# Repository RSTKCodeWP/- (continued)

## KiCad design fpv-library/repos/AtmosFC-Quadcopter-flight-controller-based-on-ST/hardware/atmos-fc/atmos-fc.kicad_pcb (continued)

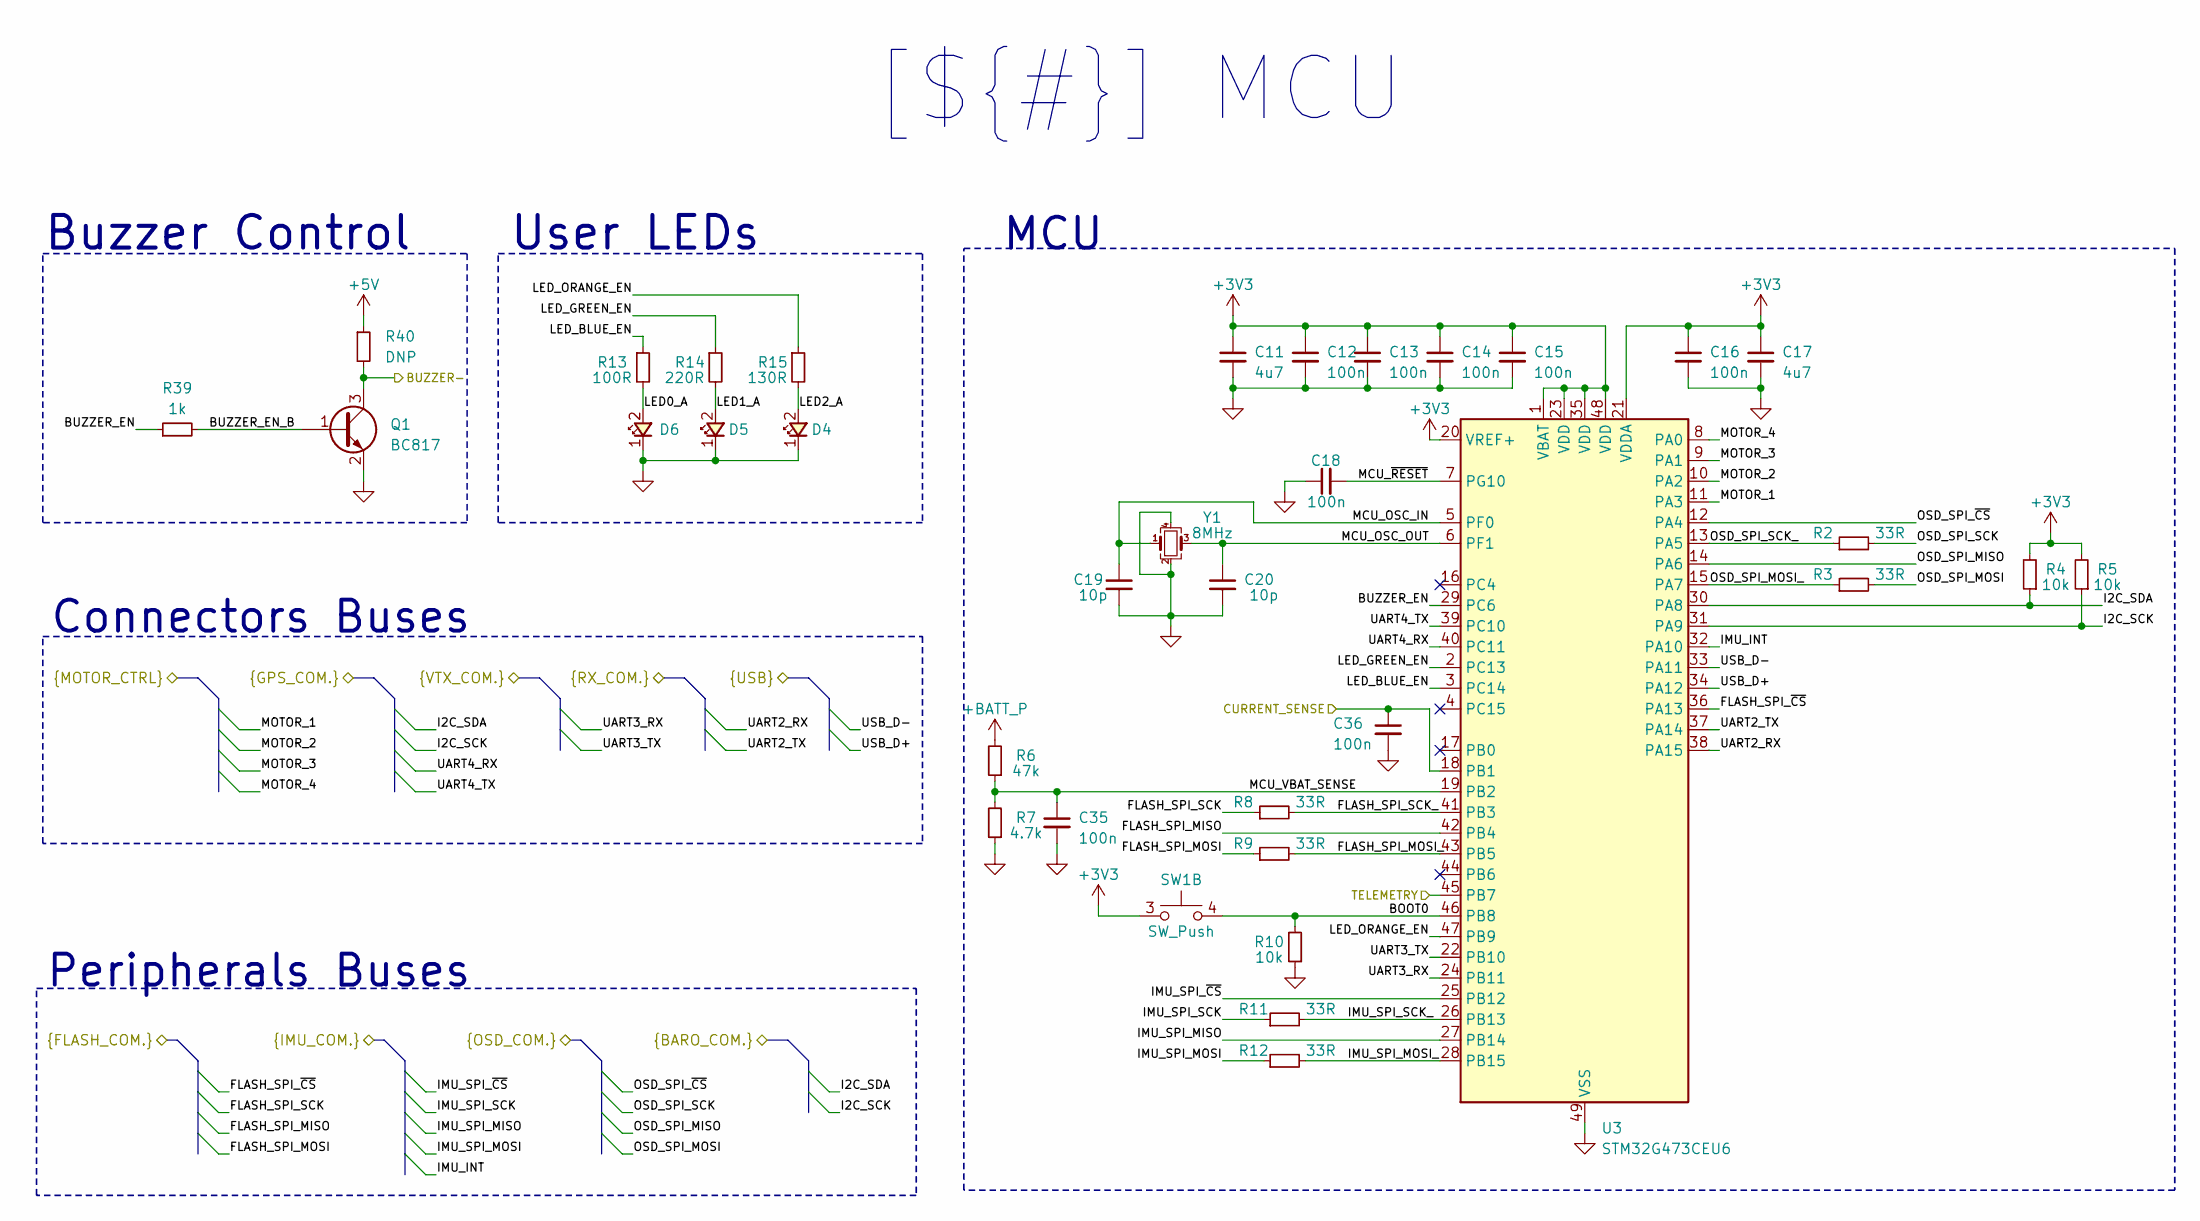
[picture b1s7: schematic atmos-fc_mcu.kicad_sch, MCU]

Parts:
C11, C17: 4u7; C_0603_1608Metric; Mfr Part Number GRM188Z71C475KE21J
C12, C13, C14, C15, C16, C18, C35, C36: 100n; C_0402_1005Metric; Mfr Part Number MSASE105SB7104KFNA01
C19, C20: 10p; C_0402_1005Metric; Mfr Part Number GRM1555C1H100JA01D
D4: LED_0603_1608Metric; Mfr Part Number LO Q976-PS-25
D5: LED_0603_1608Metric; Mfr Part Number LT Q39G-Q1OO-25-1
D6: LED_0603_1608Metric; Mfr Part Number LB Q39G-N1OO-35-1
Q1: BC817; DFN1010D-3; Mfr Part Number BC817-40QBH-QZ
R2, R3, R8, R9, R11, R12: 33R; R_0402_1005Metric; Mfr Part Number CRCW040220K0FKED
R4, R5, R10: 10k; R_0402_1005Metric; Mfr Part Number CRCW040210K0FKEDC
R6: 47k; R_0402_1005Metric; Mfr Part Number CRCW040247K0FKEDC
R7: 4.7k; R_0402_1005Metric; Mfr Part Number CRCW04024K70FKEDC
R13: 100R; R_0402_1005Metric; Mfr Part Number CRCW0402100RFKEDC
R14: 220R; R_0402_1005Metric; Mfr Part Number CRCW0402220RFKED
R15: 130R; R_0402_1005Metric; Mfr Part Number CRCW0402130RFKEDC
R39: 1k; R_0402_1005Metric; Mfr Part Number CRCW04021K00FKED
R40: DNP; R_0402_1005Metric
SW1: SW_Push; Wurth_436331045822; Mfr Part Number 436331045822
U3: STM32G473CEU6; QFN-48-1EP_7x7mm_P0.5mm_EP5.6x5.6mm; Mfr Part Number STM32G473CEU6
Y1: 8MHz; Crystal_SMD_ECS_ECX33_4Pin_3.2x2.5mm; Mfr Part Number ECS-80-10-33-CGN-TR3

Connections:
+3V3: C11.1, C12.1, C13.1, C14.1, C15.1, C16.1, C17.1, R4.2, R5.2, SW1.3 (C), U3.1 (VBAT), U3.20 (VREF+), U3.21 (VDDA), U3.23 (VDD), U3.35 (VDD), U3.48 (VDD); also elsewhere on the board
+5V: R40.1; also elsewhere on the board
+BATT_P: R6.2; also elsewhere on the board
/Connectors/BUZZER-: Q1.3 (C), R40.2; also elsewhere on the board
/Connectors/CURRENT_SENSE: C36.1, U3.18 (PB1); also elsewhere on the board
/Connectors/I2C_SCK: R5.1, U3.31 (PA9); also elsewhere on the board
/Connectors/I2C_SDA: R4.1, U3.30 (PA8); also elsewhere on the board
/Connectors/MOTOR_1: U3.11 (PA3); also elsewhere on the board
/Connectors/MOTOR_2: U3.10 (PA2); also elsewhere on the board
/Connectors/MOTOR_3: U3.9 (PA1); also elsewhere on the board
/Connectors/MOTOR_4: U3.8 (PA0); also elsewhere on the board
/Connectors/TELEMETRY: U3.45 (PB7); also elsewhere on the board
/Connectors/UART2_RX: U3.38 (PA15); also elsewhere on the board
/Connectors/UART2_TX: U3.37 (PA14); also elsewhere on the board
/Connectors/UART3_RX: U3.24 (PB11); also elsewhere on the board
/Connectors/UART3_TX: U3.22 (PB10); also elsewhere on the board
/Connectors/UART4_RX: U3.40 (PC11); also elsewhere on the board
/Connectors/UART4_TX: U3.39 (PC10); also elsewhere on the board
/Connectors/USB_D+: U3.34 (PA12); also elsewhere on the board
/Connectors/USB_D-: U3.33 (PA11); also elsewhere on the board
/Flash Memory/FLASH_SPI_MISO: U3.42 (PB4); also elsewhere on the board
/Flash Memory/FLASH_SPI_MOSI: R9.1; also elsewhere on the board
/Flash Memory/FLASH_SPI_SCK: R8.1; also elsewhere on the board
/Flash Memory/FLASH_SPI_~CS: U3.36 (PA13); also elsewhere on the board
/IMU/IMU_INT: U3.32 (PA10); also elsewhere on the board
/IMU/IMU_SPI_MISO: U3.27 (PB14); also elsewhere on the board
/IMU/IMU_SPI_MOSI: R12.1; also elsewhere on the board
/IMU/IMU_SPI_SCK: R11.1; also elsewhere on the board
/IMU/IMU_SPI_~CS: U3.25 (PB12); also elsewhere on the board
/MCU/BOOT0: R10.2, SW1.4 (D), U3.46 (PB8)
/MCU/BUZZER_EN: R39.1, U3.29 (PC6)
/MCU/BUZZER_EN_B: Q1.1 (B), R39.2
/MCU/FLASH_SPI_MOSI_: R9.2, U3.43 (PB5)
/MCU/FLASH_SPI_SCK_: R8.2, U3.41 (PB3)
/MCU/IMU_SPI_MOSI_: R12.2, U3.28 (PB15)
/MCU/IMU_SPI_SCK_: R11.2, U3.26 (PB13)
/MCU/LED0_A: D6.2, R13.2
/MCU/LED1_A: D5.2, R14.2
/MCU/LED2_A: D4.2, R15.2
/MCU/LED_BLUE_EN: R13.1, U3.3 (PC14)
/MCU/LED_GREEN_EN: R14.1, U3.2 (PC13)
/MCU/LED_ORANGE_EN: R15.1, U3.47 (PB9)
/MCU/MCU_OSC_IN: C19.1, U3.5 (PF0), Y1.1
/MCU/MCU_OSC_OUT: C20.1, U3.6 (PF1), Y1.3
/MCU/MCU_VBAT_SENSE: C35.1, R6.1, R7.2, U3.19 (PB2)
/MCU/MCU_~RESET: C18.2, U3.7 (PG10)
/MCU/OSD_SPI_MISO: U3.14 (PA6); also elsewhere on the board
/MCU/OSD_SPI_MOSI: R3.2; also elsewhere on the board
/MCU/OSD_SPI_MOSI_: R3.1, U3.15 (PA7)
/MCU/OSD_SPI_SCK: R2.2; also elsewhere on the board
/MCU/OSD_SPI_SCK_: R2.1, U3.13 (PA5)
/MCU/OSD_SPI_~CS: U3.12 (PA4); also elsewhere on the board
GND: C11.2, C12.2, C13.2, C14.2, C15.2, C16.2, C17.2, C18.1, C19.2, C20.2, C35.2, C36.2, D4.1, D5.1, D6.1, Q1.2 (E), R7.1, R10.1, U3.49 (VSS), Y1.2, Y1.4; also elsewhere on the board

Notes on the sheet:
[${#}] ${TITLE}
MCU
Peripherals Buses
Buzzer Control
Connectors Buses
User LEDs

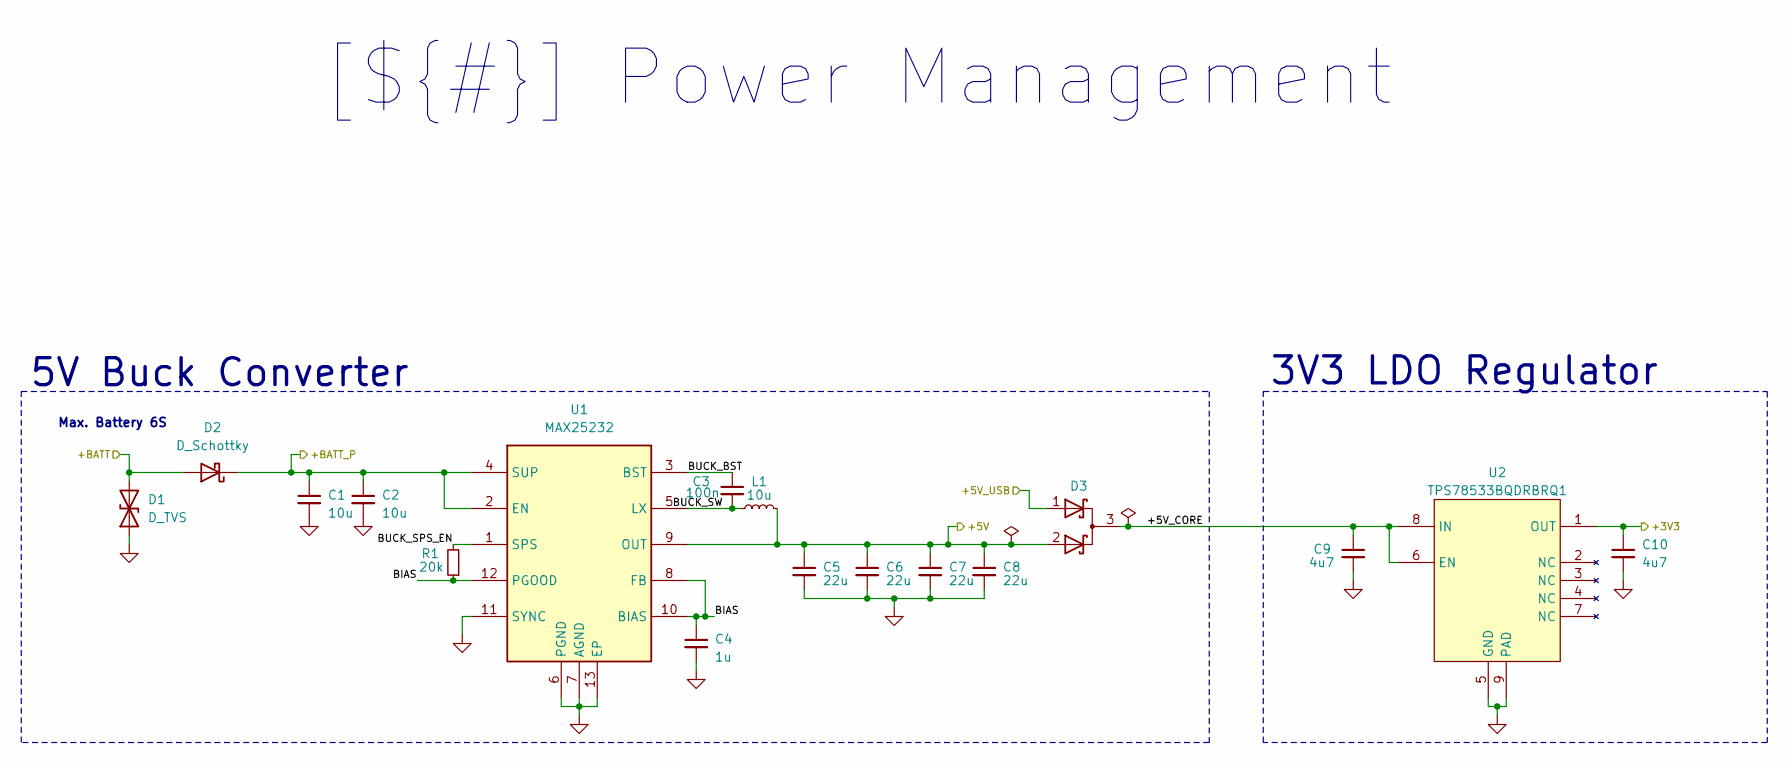
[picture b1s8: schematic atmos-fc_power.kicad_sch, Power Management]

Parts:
C1, C2: 10u; C_1206_3216Metric; Mfr Part Number MCJCG31LBB7106KTPA01
C3: 100n; C_0402_1005Metric; Mfr Part Number MSASE105SB7104KFNA01
C4: 1u; C_0603_1608Metric; Mfr Part Number MSAST168SB7105KTNA01
C5, C6, C7, C8: 22u; C_1206_3216Metric; Mfr Part Number MSASE31LBB7226MTNA01
C9, C10: 4u7; C_0603_1608Metric; Mfr Part Number GRM188Z71C475KE21J
D1: D_TVS; D_SOD-882; Mfr Part Number PESD30VF1BBL-QYL
D2: D_Schottky; DFN3820A; Mfr Part Number V7N103HM3/I
D3: PMEG2020CPASX; HUSON-3-1EP_2x2mm_P1.3mm_EP1.1x1.6mm; Mfr Part Number PMEG2020CPASX
L1: 10u; L_Bourns_SRP5030CC; Mfr Part Number SRP5030CC-100M
R1: 20k; R_0402_1005Metric; Mfr Part Number CRCW040220K0FKED
U1: MAX25232; Maxim_TDFN-12-1EP_3x3mm_P0.5mm_EP1.7x2.5mm_ThermalVias; Mfr Part Number MAX25232ATCD_V+
U2: TPS78533BQDRBRQ1; VSON-8-1EP_3x3mm_P0.65mm_EP1.65x2.4mm_ThermalVias; Mfr Part Number TPS78533BQWDRBRQ1

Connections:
+3V3: C10.1, U2.1 (OUT); also elsewhere on the board
+5V: C5.1, C6.1, C7.1, C8.1, D3.2 (K), L1.2, U1.9 (OUT); also elsewhere on the board
+BATT_P: C1.1, C2.1, D2.1 (K), U1.2 (EN), U1.4 (SUP); also elsewhere on the board
/Connectors/+5V_USB: D3.1 (K); also elsewhere on the board
/Connectors/+BATT: D1.2 (A2), D2.2 (A); also elsewhere on the board
/Power Management/+5V_CORE: C9.1, D3.3 (A), U2.6 (EN), U2.8 (IN)
/Power Management/BIAS: C4.1, R1.1, U1.8 (FB), U1.10 (BIAS), U1.12 (PGOOD)
/Power Management/BUCK_BST: C3.1, U1.3 (BST)
/Power Management/BUCK_SPS_EN: R1.2, U1.1 (SPS)
/Power Management/BUCK_SW: C3.2, L1.1, U1.5 (LX)
GND: C1.2, C2.2, C4.2, C5.2, C6.2, C7.2, C8.2, C9.2, C10.2, D1.1 (A1), U1.6 (PGND), U1.7 (AGND), U1.11 (SYNC), U1.13 (EP), U2.5 (GND), U2.9 (PAD); also elsewhere on the board

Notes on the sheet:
[${#}] ${TITLE}
5V Buck Converter
3V3 LDO Regulator
Max. Battery 6S

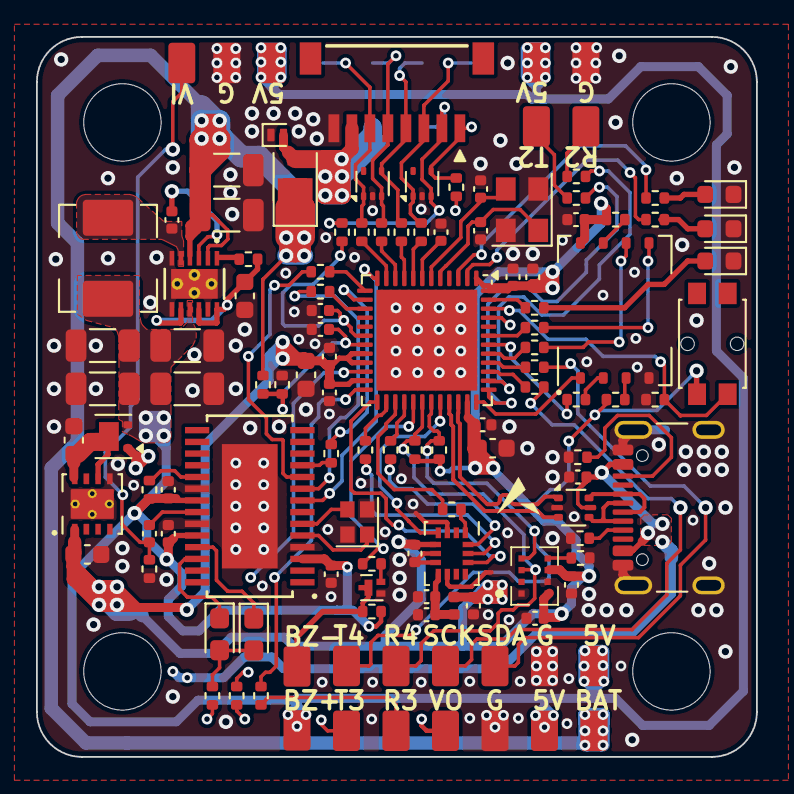
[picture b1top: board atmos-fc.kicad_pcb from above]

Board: 4 copper layers, 40.0 x 40.0 mm, 110 parts (1 on the bottom side), 90 nets.

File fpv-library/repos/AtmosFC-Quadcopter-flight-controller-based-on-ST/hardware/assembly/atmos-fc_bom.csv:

"Reference","Value","Qty","Description","Manufacturer","Mfr Part Number"
"C19,C20","10p","2","Multilayer Ceramic Capacitors MLCC - SMD/SMT 10 pF 50 VDC 5% 0402 C0G (NP0)","Murata Electronics","GRM1555C1H100JA01D"
"C30","10n","1","Multilayer Ceramic Capacitors MLCC - SMD/SMT 0.01 uF 25 VDC 2% 0402 C0G (NP0)","Murata Electronics","GRM1555C1E103GE01D"
"C3,C12,C13,C14,C15,C16,C18,C21,C22,C23,C24,C29,C31,C32,C33,C34","100n","16","Multilayer Ceramic Capacitors MLCC - SMD/SMT 16V 0.1uF X7R 0402 10 %","TAIYO YUDEN","MSASE105SB7104KFNA01"
"C4","1u","1","Multilayer Ceramic Capacitors MLCC - SMD/SMT 25V 1uF X7R 0603 10 %","TAIYO YUDEN","MSAST168SB7105KTNA01"
"C1,C2","10u","2","Multilayer Ceramic Capacitors MLCC - SMD/SMT 35V 10uF X7R 1206 10 %","TAIYO YUDEN","MCJCG31LBB7106KTPA01"
"L1","10u","1","Power Inductors - SMD Ind,5.7x5.2x2.8mm,10uH+/-20%,2.8A,shd","Bourns","SRP5030CC-100M"
"C5,C6,C7,C8","22u","4","Multilayer Ceramic Capacitors MLCC - SMD/SMT 16V 22uF X7R 1206 20 %","TAIYO YUDEN","MSASE31LBB7226MTNA01"
"C25,C26","47u","2","Tantalum Capacitors - Solid SMD 10V 47uF 0805 Tol +/-20%","KYOCERA AVX","F981A476MSAAS1"
"R2,R3,R8,R9,R11,R12,R17,R20,R21,R27,R28,R29,R30,R31,R32,R33,R34,R35,R36,R37,R38","33R","21","Thick Film Resistors - SMD 1/16watt 33ohms 1% 100ppm","Vishay / Dale","CRCW040220K0FKED"
"R16,R19","75R","2","Thick Film Resistors - SMD 1/16watt 75ohms 1%","Vishay / Dale","CRCW040275R0FKED"
"R13","100R","1","Thick Film Resistors - SMD 1/16watt 100ohms 1% Commercial Use","Vishay / Dale","CRCW0402100RFKEDC"
"R15","130R","1","Thick Film Resistors - SMD 1/16watt 130ohms 1% Commercial Use","Vishay / Dale","CRCW0402130RFKEDC"
"R14","220R","1","Thick Film Resistors - SMD 1/16watt 220ohms 1%","Vishay / Dale","CRCW0402220RFKED"
"R39","1k","1","Thick Film Resistors - SMD 1/16watt 1.0Kohms 1%","Vishay / Dale","CRCW04021K00FKED"
"R7","4.7k","1","Thick Film Resistors - SMD 1/16watt 4.7Kohms 1% Commercial Use","Vishay / Dale","CRCW04024K70FKEDC"
"R4,R5,R10,R18","10k","4","Thick Film Resistors - SMD 1/16watt 10Kohms 1% Commercial Use","Vishay / Dale","CRCW040210K0FKEDC"
"R1","20k","1","Thick Film Resistors - SMD 1/16watt 20Kohms 1%","Vishay / Dale","CRCW040220K0FKED"
"R6,R22,R23,R24","47k","4","Thick Film Resistors - SMD 1/16watt 47Kohms 1% Commercial Use","Vishay / Dale","CRCW040247K0FKEDC"
"Y1","8MHz","1","Crystals 8MHz 10 pF 3225 TOL +/-10, STAB +/-30 ppm, -40 +85 C, 400O","ECS","ECS-80-10-33-CGN-TR3"
"Y2","27MHz","1","Crystals 27MHz 8pF AEC-Q200 2 .05X1.65X.45mm","KYOCERA AVX","CX2016SA27000D0GSSCC"
"FB1","120R@100MHz","1","Ferrite Beads 0402 120ohm 25% 5A AEC-Q200","Murata Electronics","BLM15PX121BH1D"
"C27,C28","2u2","2","Multilayer Ceramic Capacitors MLCC - SMD/SMT 2.2 uF 10 VDC 10% 0402 X7S","Murata Electronics","GRM155C71A225KE11D"
"C9,C10,C11,C17","4u7","4","Multilayer Ceramic Capacitors MLCC - SMD/SMT 4.7 uF 16 VDC 10% 0603 X7R","Murata Electronics","GRM188Z71C475KE21J"
"R25,R26","5k1","2","Thick Film Resistors - SMD 1/16watt 5.1Kohms 1%","Vishay / Dale","CRCW04025K10FKED"
"Q1","BC817","1","Bipolar Transistors - BJT SOT8015 45V .5A NPN GP TRANS","Nexperia","BC817-40QBH-QZ"
"D2","D_Schottky","1","Schottky Diodes & Rectifiers 7A, 100V, DFN3820A TRENCH SKY RECT.","Vishay Semiconductors ","V7N103HM3/I"
"D1","D_TVS","1","ESD Protection Diodes / TVS Diodes ESD 30V BI","Nexperia","PESD30VF1BBL-QYL"
"R40","DNP","1","","",""
"U7","DPS368XTSA1","1","Digital XENSIVTM barometric pressure sensor"," Infineon Technologies","DPS368XTSA1"
"U5","ICM-42688-P","1","High Precision 6-Axis MEMS MotionTrackingTM Device","TDK InvenSense","ICM-42688-P"
"J2","JST-SH 8p","1","Headers & Wire Housings SR HEADER (SMT SIDE)","JST Sales America Inc.","SM08B-SRSS-TB"
"U4","MAX7456","1","Single-Channel Monochrome On-Screen Display with Integrated EEPROM","Analog Devices","MAX7456EUI+"
"U1","MAX25232","1","36V, 3A Mini Buck Converters with 3.5uA IQ","Analog Devices","MAX25232ATCD_V+"
"D3","PMEG2020CPASX","1","Schottky Diodes & Rectifiers RECTIFIER SOT1061/HUSON3","Nexperia","PMEG2020CPASX"
"D7,D8","SP1001-04XTG","2","8pF 15kV Unidirectional TVS Array","Littlefuse","SP1001-04XTG"
"U3","STM32G473CEU6","1","ARM Microcontrollers - MCU Mainstream Arm Cortex-M4 MCU 170MHz 512Kbytes of Flash Math Accel, High Analog","STMicroelectronics","STM32G473CEU6"
"SW1","SW_Push","1","Tactile Switches Tact Switch SMT 1.65mm","Wurth Elektronik","436331045822"
"U2","TPS78533BQDRBRQ1","1","TPS785-Q1 Automotive, 1-A, High-PSRR Low-Dropout Voltage Regulator With High Accuracy and Enable","Texas Instruments","TPS78533BQWDRBRQ1"
"J3","USB_C_Receptacle_USB2.0_16P","1","USB 2.0-only 16P Type-C Receptacle connector","GCT","USB4105-GF-A"
"U8","USBLC6-2P6","1","Very low capacitance ESD protection diode, 2 data-line, SOT-666","STMicroelectronics","USBLC6-2P6"
"U6","W25Q256JVE","1","3V 256M-BIT SERIAL FLASH MEMORY WITH DUAL/QUAD SPI","Winbond","W25Q256JVEIQ "
"D4,D5,D6","~","3","-- valeurs mixtées --","ams OSRAM","-- valeurs mixtées --"
